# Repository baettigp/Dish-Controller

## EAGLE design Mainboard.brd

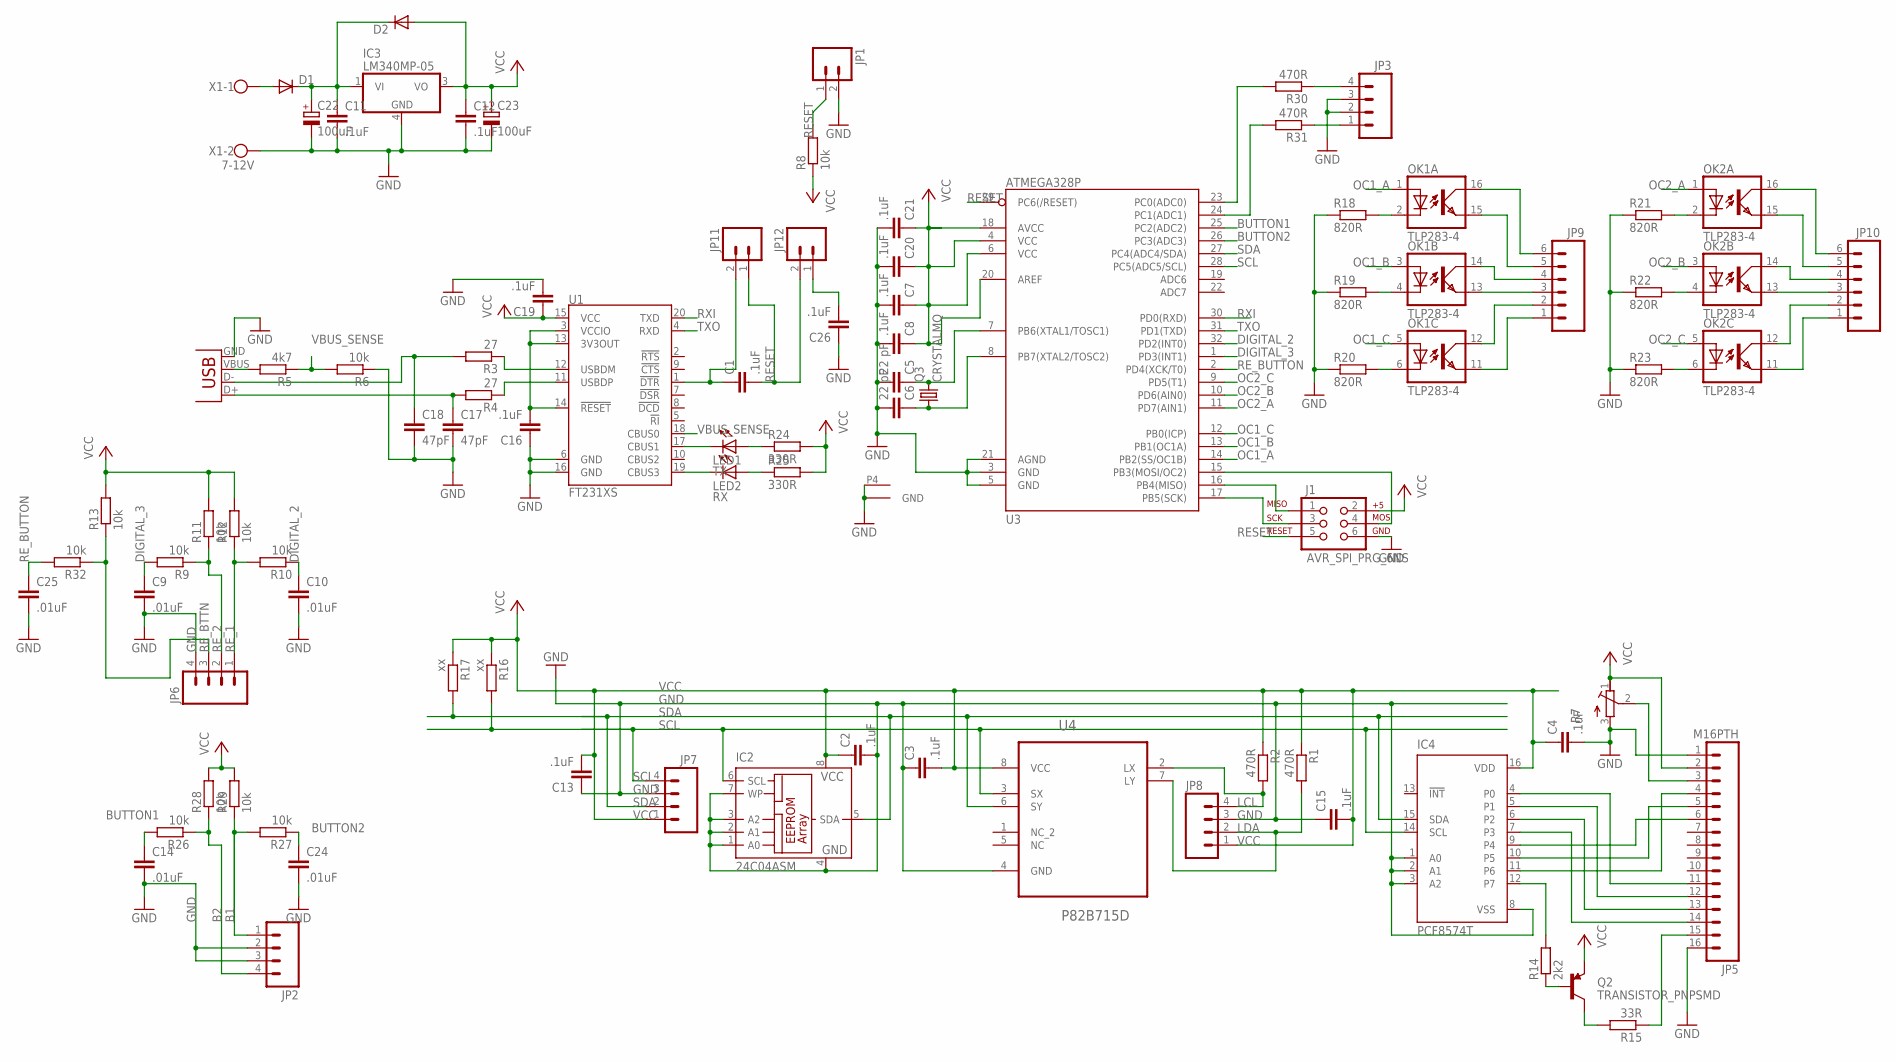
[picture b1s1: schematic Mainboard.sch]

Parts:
C1, C2, C3, C4, C7, C8, C11, C12, C13, C15, C16, C19, C20, C21, C26: .1uF; C0805; MPN 2222 370 21104
C5, C6: 22 pF; C0805; MPN 02013A220JAT2A
C9, C10, C14, C24, C25: .01uF; C0805; MPN B32529C103K
C17, C18: 47pF; C0805
C22, C23: 100uF; PANASONIC_D
D1, D2: DIODE-MELF-MLL41; MELF-MLL41
IC2: 24C04ASM; SO-08M
IC3: LM340MP-05; SOT223
IC4: PCF8574T; SO16W
J1: AVR_SPI_PRG_6NS; 2X3-NS
JP1: M02POLAR; MOLEX-1X2
JP2, JP6, JP7, JP8: M04POLAR; MOLEX-1X4
JP3: M04PTH; 1X04
JP4: USB-B; USB-B-PTH
JP5: M16PTH; 1X16
JP9, JP10: M06POLAR; MOLEX-1X6
JP11, JP12: M02PTH; 1X02
LED1: TX; CHIPLED_0805
LED2: RX; CHIPLED_0805
OK1, OK2: TLP283-4; MINI-FLAT-16
Q2: TRANSISTOR_PNPSMD; SOT23-3
Q3: CRYSTALMQ; MQ
R1, R2: 470R; R0805
R3, R4: 27; R0805
R5: 4k7; R0805
R6, R8, R9, R10, R11, R12, R13, R26, R27, R28, R29, R32: 10k; R0805; MPN 043P103
R7: R-TRIMM3314G; RTRIM3314G
R14: 2k2; R0805; MPN 043P103
R15: 33R; R0805; MPN 043P103
R16, R17: xx; R0805
R18, R19, R20, R21, R22, R23: 820R; R0805
R24, R25: 330R; R0805
R30, R31: 470R; R0805; MPN 043P103
U1: FT231XS; SSOP20_L
U3: ATMEGA328P; TQFP32-08
U4: P82B715D; SOIC127P600X175-8N
X1: 7-12V; W237-102

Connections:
B1: JP2.1, R27.2, R29.1
B2: JP2.4, R26.1, R28.1
BUTTON1: C14.1, R26.2, U3.25 (PC2(ADC2))
BUTTON2: C24.1, R27.1, U3.26 (PC3(ADC3))
D+: C17.1, JP4.D+, R4.2
D-: C18.1, JP4.D-, R3.2
DIGITAL_2: C10.1, R10.1, U3.32 (PD2(INT0))
DIGITAL_3: C9.1, R9.2, U3.1 (PD3(INT1))
GND: C2.2, C3.1, C4.2, C5.2, C6.2, C7.2, C8.2, C9.2, C10.2, C11.2, C12.2, C13.1, C14.2, C15.1, C16.1, C17.2, C18.2, C19.2, C20.2, C21.2, C22.-, C23.-, C24.2, C25.2, C26.1, IC2.1 (A0), IC2.2 (A1), IC2.3 (A2), IC2.4 (GND), IC2.7 (WP), IC3.4 (GND), IC4.1 (A0), IC4.2 (A1), IC4.3 (A2), IC4.8 (VSS), J1.6, JP1.2, JP2.2, JP2.3, JP3.2, JP3.3, JP4.GND, JP5.1, JP5.16, JP6.4, JP7.3, JP8.3, Q3.P2 (GND), Q3.P4 (GND1), R6.1, R7.3 (A), R18.1, R19.1, R20.1, R21.1, R22.1, R23.1, U1.6 (GND), U1.16 (GND), U3.3 (GND), U3.5 (GND), U3.21 (AGND), U4.4 (GND), X1.2
LCL: JP8.4, R2.2, U4.2 (LX)
LDA: JP8.2, R1.2, U4.7 (LY)
MISO: J1.1, U3.16 (PB4(MISO))
MOSI: J1.4, U3.15 (PB3(MOSI/OC2))
unnamed: LED2.C, U1.19 (CBUS3)
unnamed: C1.1, JP11.2, U1.1 (!DTR)
unnamed: C16.2, U1.3 (VCCIO), U1.13 (3V3OUT), U1.14 (!RESET)
unnamed: JP3.4, R30.1
unnamed: R3.1, U1.12 (USBDM)
unnamed: R4.1, U1.11 (USBDP)
unnamed: JP3.1, R31.1
unnamed: R30.2, U3.23 (PC0(ADC0))
unnamed: R31.2, U3.24 (PC1(ADC1))
unnamed: Q2.1 (B), R14.1
unnamed: JP9.1, OK1.11 (EMIT)
unnamed: JP5.3, R7.2 (S)
unnamed: C11.1, C22.+, D1.C, D2.C, IC3.1 (VI)
unnamed: IC4.11 (P6), JP5.4
unnamed: IC4.10 (P5), JP5.5
unnamed: IC4.9 (P4), JP5.6
unnamed: IC4.4 (P0), JP5.11
unnamed: IC4.5 (P1), JP5.12
unnamed: IC4.6 (P2), JP5.13
unnamed: IC4.7 (P3), JP5.14
unnamed: C5.1, Q3.P3 (2), U3.7 (PB6(XTAL1/TOSC1))
unnamed: C6.1, Q3.P1 (1), U3.8 (PB7(XTAL2/TOSC2))
unnamed: IC4.12 (P7), R14.2
unnamed: JP5.15, R15.1
unnamed: Q2.3 (C), R15.2
unnamed: OK1.2 (C), R18.2
unnamed: OK1.4 (C), R19.2
unnamed: OK1.6 (C), R20.2
unnamed: OK2.2 (C), R21.2
unnamed: OK2.4 (C), R22.2
unnamed: OK2.6 (C), R23.2
unnamed: LED1.C, U1.17 (CBUS1)
unnamed: D1.A, X1.1
unnamed: JP9.2, OK1.12 (COL)
unnamed: LED1.A, R24.1
unnamed: LED2.A, R25.1
unnamed: JP9.3, OK1.13 (EMIT)
unnamed: JP9.4, OK1.14 (COL)
unnamed: JP9.5, OK1.15 (EMIT)
unnamed: JP9.6, OK1.16 (COL)
unnamed: JP10.3, OK2.13 (EMIT)
unnamed: JP10.4, OK2.14 (COL)
unnamed: JP10.5, OK2.15 (EMIT)
unnamed: JP10.6, OK2.16 (COL)
unnamed: JP10.2, OK2.12 (COL)
unnamed: JP10.1, OK2.11 (EMIT)
unnamed: C26.2, JP12.1
OC1_A: OK1.1 (A), U3.14 (PB2(SS/OC1B))
OC1_B: OK1.3 (A), U3.13 (PB1(OC1A))
OC1_C: OK1.5 (A), U3.12 (PB0(ICP))
OC2_A: OK2.1 (A), U3.11 (PD7(AIN1))
OC2_B: OK2.3 (A), U3.10 (PD6(AIN0))
OC2_C: OK2.5 (A), U3.9 (PD5(T1))
RESET: C1.2, J1.5, JP1.1, JP11.1, JP12.2, R8.2, U3.29 (PC6(/RESET))
RE_1: JP6.1, R10.2, R12.1
RE_2: JP6.2, R9.1, R11.1
RE_BTTN: JP6.3, R13.1, R32.1
RE_BUTTON: C25.1, R32.2, U3.2 (PD4(XCK/T0))
RXI: U1.20 (TXD), U3.30 (PD0(RXD))
SCK: J1.3, U3.17 (PB5(SCK))
SCL: IC2.6 (SCL), IC4.14 (SCL), JP7.4, R16.2, U3.28 (PC5(ADC5/SCL)), U4.3 (SX)
SDA: IC2.5 (SDA), IC4.15 (SDA), JP7.2, R17.2, U3.27 (PC4(ADC4/SDA)), U4.6 (SY)
TXO: U1.4 (RXD), U3.31 (PD1(TXD))
VBUS: JP4.VBUS, R5.2
VBUS_SENSE: R5.1, R6.2, U1.18 (CBUS0)
VCC: C2.1, C3.2, C4.1, C7.1, C8.1, C12.1, C13.2, C15.2, C19.1, C20.1, C21.1, C23.+, D2.A, IC2.8 (VCC), IC3.3 (VO), IC4.16 (VDD), J1.2, JP5.2, JP7.1, JP8.1, Q2.2 (E), R1.1, R2.1, R7.1 (E), R8.1, R11.2, R12.2, R13.2, R16.1, R17.1, R24.2, R25.2, R28.2, R29.2, U1.15 (VCC), U3.4 (VCC), U3.6 (VCC), U3.18 (AVCC), U3.20 (AREF), U4.8 (VCC)

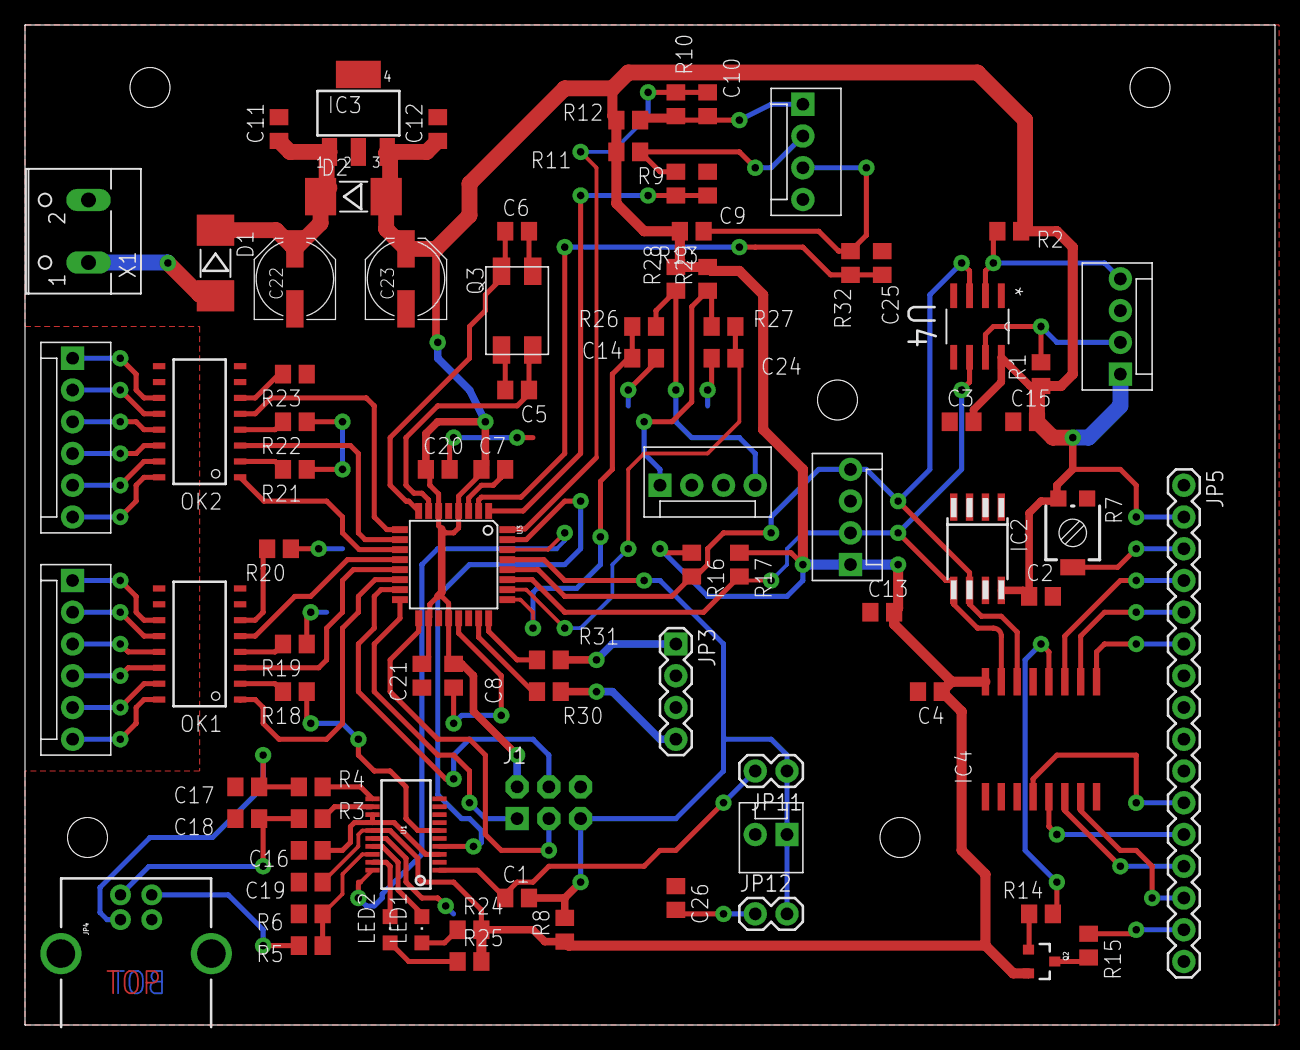
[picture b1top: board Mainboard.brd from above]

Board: 2 copper layers, 100.0 x 80.0 mm, 86 parts (0 on the bottom side), 79 nets.

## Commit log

2013-09-02 First Version

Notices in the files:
parts and their libraries:
SparkFun-DigitalIC: Licensing: CC v3.0 Share-Alike You are welcome to use this library for commercial purposes.
